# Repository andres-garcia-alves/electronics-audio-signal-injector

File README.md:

# Audio Signal Injector

A simple signal injector for faults diagnosing in audio equipment.  
Schematics diagram + PCB diagram (KiCAD 9) and case 3D model (Blender) are also provided.  

Based on the Espacio de Cesar's video: [Audio Signal Injector](https://www.youtube.com/watch?v=kp08ScxISPk). [spanish]

&nbsp;

### Notes:

- Power input: 5-12 VDC
- Turn the potentiometer to adjust the volume.
- Turn de trimmer to adjust the generated audio frecuency.
- Use the probes on speakers, buzzers and so on to diagnose audio problems.

&nbsp;

### List of Materials

- 1 x IC NE555
- 1 x Electrolitic capacitor 1uF
- 1 x Capacitor 100nF
- 1 x Capacitor 56nF
- 1 x Resistor 3.3k ohms
- 1 x Trimmer 50k ohms
- 1 x Potentiometer 10k ohms
- 1 x LED
- 1 x Resistor 470 ohms
- 1 x Rocker Button (power on/off)
- 2 x Banana connector
- 1 x Bornier connector 2-pins / JST connector 2-pins
- 1 x 9V battery / 2 x 18650 battery
- 1 x 9V battery holder / 1 x 18650 battery holder x2
- Wires

&nbsp;

### Screenshots

| Breadboard                                           | Assembly                                             |
|------------------------------------------------------|------------------------------------------------------|
|                   |                     |

| Assembly                                             | Assembly                                             |
|------------------------------------------------------|------------------------------------------------------|
|                     |                     |

| Schematics Diagram                                   | PCB Diagram                                          |
|------------------------------------------------------|------------------------------------------------------|
|              |                     |

| PCB Render 3D                                        | PCB Render 3D                                        |
|------------------------------------------------------|------------------------------------------------------|
|             |            |

| Case 3D Model                                        | Project Final                                        |
|------------------------------------------------------|------------------------------------------------------|
|                   |                    |

See 'Resources' folder for more pictures & videos of the project.

&nbsp;

### Version History

v1.0 (2026.01.06) - Adding schematics and PCB.  
v1.1 (2026.01.07) - Adding case 3D model.  
v1.2 (2026.01.09) - Adding folder 'Resources'.  

&nbsp;

This source code is licensed under GPL v3.0  
Please send me your feedback about this project: andres.garcia.alves@gmail.com

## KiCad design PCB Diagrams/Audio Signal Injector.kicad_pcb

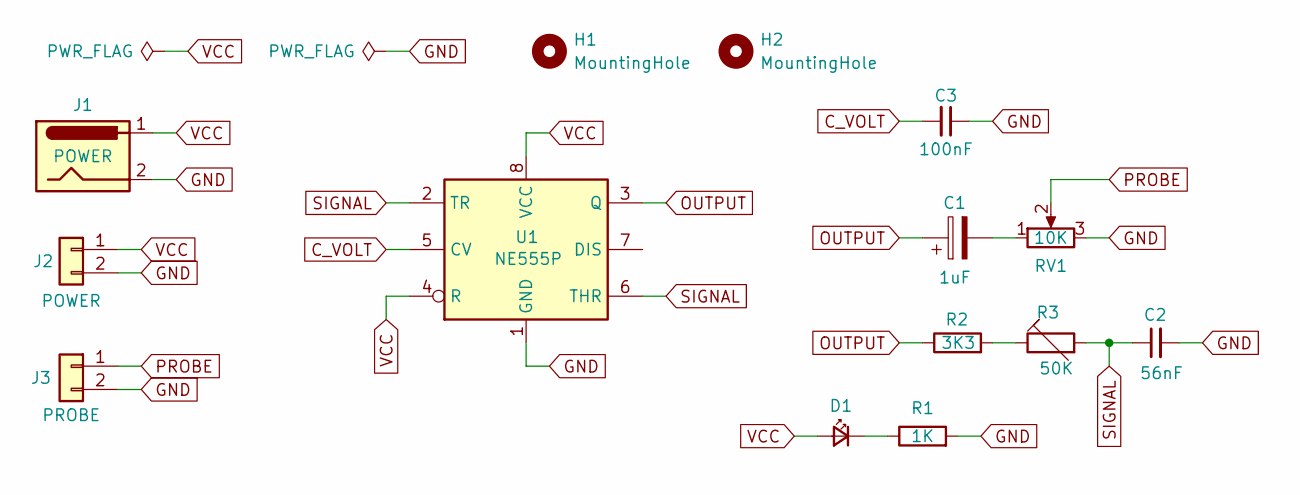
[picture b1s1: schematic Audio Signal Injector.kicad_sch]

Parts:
C1: 1uF; C_Radial_D6.3mm_H11.0mm_P2.50mm
C2: 56nF; C_Disc_D6.0mm_W2.5mm_P5.00mm; Voltage 1kV; Tolerance 100%
C3: 100nF; C_Disc_D6.0mm_W2.5mm_P5.00mm; Voltage 1kV; Tolerance 100%
D1: LED; LED_D3.0mm
H1, H2: MountingHole; MountingHole_2.2mm_M2_ISO7380
J1: POWER; BarrelJack_Horizontal
J2: POWER; JST_EH_B2B-EH-A_1x02_P2.50mm_Vertical
J3: PROBE; TerminalBlock_Phoenix_PT-1,5-2-5.0-H_1x02_P5.00mm_Horizontal
R1: 1K; R_Axial_DIN0207_L6.3mm_D2.5mm_P2.54mm_Vertical
R2: 3K3; R_Axial_DIN0207_L6.3mm_D2.5mm_P2.54mm_Vertical
R3: 50K; Trimmer_Piher_PT6_Vertical
RV1: 10K; Potenciometer_PTV09A
U1: NE555P; DIP-8_W7.62mm

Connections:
C_VOLT: C3.2, U1.5 (CV)
GND: C2.2, C3.1, J1.2, J2.2, J3.2, R1.2, RV1.3, U1.1 (GND)
unnamed: C1.2, RV1.1
unnamed: D1.1 (K), R1.1
unnamed: R2.2, R3.1
OUTPUT: C1.1, R2.1, U1.3 (Q)
PROBE: J3.1, RV1.2
SIGNAL: C2.1, R3.2, U1.2 (TR), U1.6 (THR)
VCC: D1.2 (A), J1.1, J2.1, U1.4 (R), U1.8 (VCC)

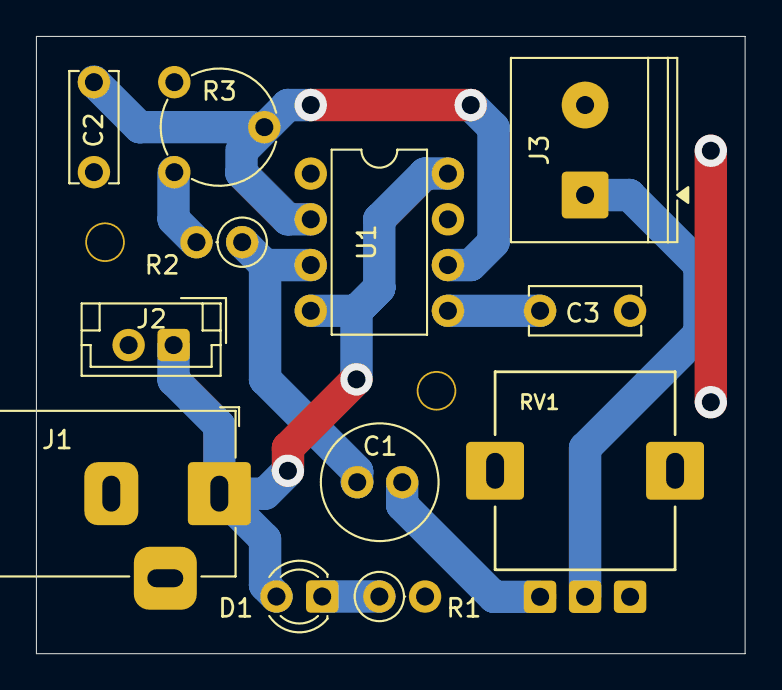
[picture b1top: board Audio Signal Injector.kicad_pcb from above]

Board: 2 copper layers, 39.4 x 34.3 mm, 14 parts (0 on the bottom side), 9 nets.

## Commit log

2026-01-07 Adding case 3D model
2026-01-07 Adding project resources
2026-01-09 Adding folder 'Resources'
